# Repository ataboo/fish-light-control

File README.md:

# Fish Light Control

ESP32 controlling the brightness of addressable LEDS depending on the time of day.  Intended as lighting for a fish tank.

## Hardware

- ESP32 dev kit
- WS2812B light strip
- SN74HCT04N HEX inverter

SN74HCT04N shifts the signal level from 3.3v to 5v by inverting twice.

## Install

Setup typical ESP-IDF environment (tested on IDF 4.2).  Menu options for `ESP-Fish-Light`.  Setup SSID/PW for time synchronizations. Set sunrise/set start/end in format `hhmm`.  Set timezone according to POSIX rules.  Set color of full brightness.

## Behaviour

Device will sleep until the start of sunrise or sunset, then wake every minute to update the color during the transitions.  WIFI will be activated on first start as time establishment is required, then after light update if 24 hours has passed since the last update.

Blue lights mean initial loading/time sync.  Red lights mean failed initial load.

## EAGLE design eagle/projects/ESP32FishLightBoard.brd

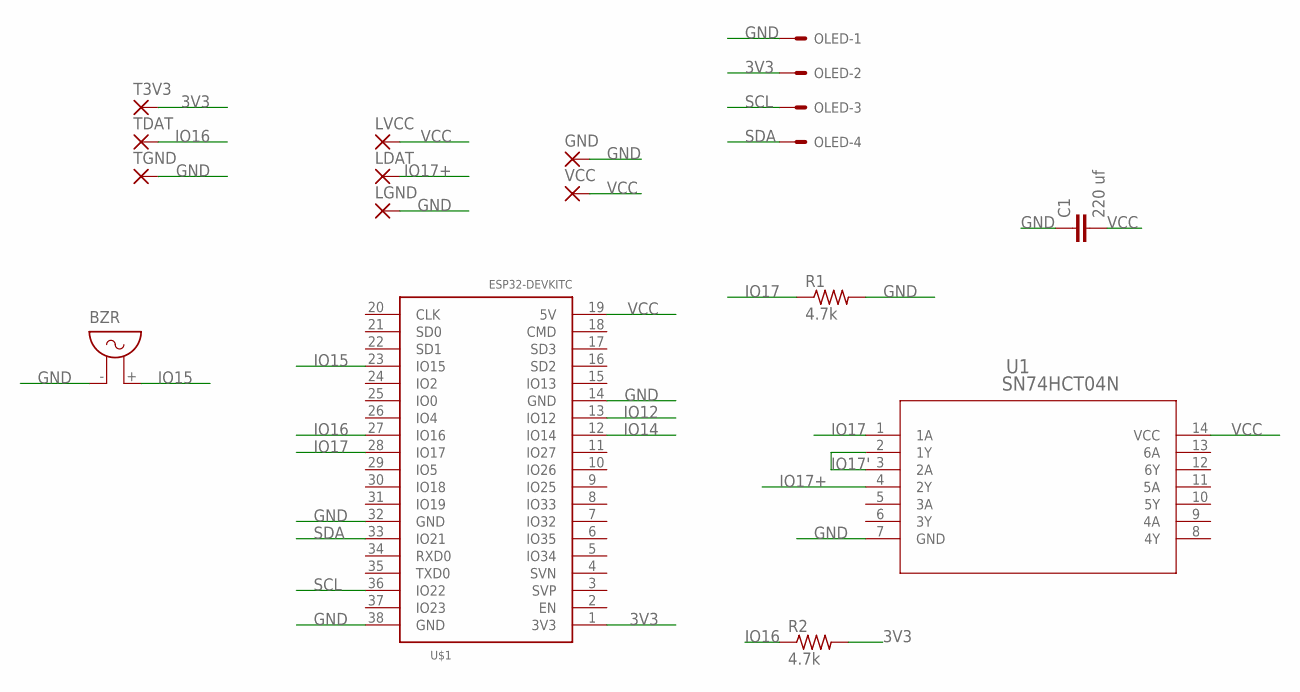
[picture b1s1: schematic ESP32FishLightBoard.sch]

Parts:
BZR: F/QMX
C1: 220 uf; C2.5-3
GND: WIREPAD2,54/1,0; 2,54/1,0
LDAT: WIREPAD2,54/1,0; 2,54/1,0
LGND: WIREPAD2,54/1,0; 2,54/1,0
LVCC: WIREPAD2,54/1,0; 2,54/1,0
OLED: 22-27-2041-04; 6410-04
R1, R2: 4.7k; 0805-THM
T3V3: WIREPAD2,54/1,0; 2,54/1,0
TDAT: WIREPAD2,54/1,0; 2,54/1,0
TGND: WIREPAD2,54/1,0; 2,54/1,0
U1: SN74HCT04N; N14
U$1: ESP32DEVKITC-LIGHT; ESP32-DEVKITC-LIGHT
VCC: WIREPAD2,54/1,0; 2,54/1,0

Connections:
3V3: OLED.2, R2.2, T3V3.1, U$1.1 (3V3)
GND: BZR.- (1), C1.1, GND.1, LGND.1, OLED.1, R1.2, TGND.1, U1.7 (GND), U$1.14 (GND), U$1.32 (GND), U$1.38 (GND)
IO12: U$1.13 (IO12)
IO14: U$1.12 (IO14)
IO15: BZR.+ (2), U$1.23 (IO15)
IO16: R2.1, TDAT.1, U$1.27 (IO16)
IO17: R1.1, U1.1 (1A), U$1.28 (IO17)
IO17': U1.2 (1Y), U1.3 (2A)
IO17+: LDAT.1, U1.4 (2Y)
SCL: OLED.3, U$1.36 (IO22)
SDA: OLED.4, U$1.33 (IO21)
VCC: C1.2, LVCC.1, U1.14 (VCC), U$1.19 (5V), VCC.1

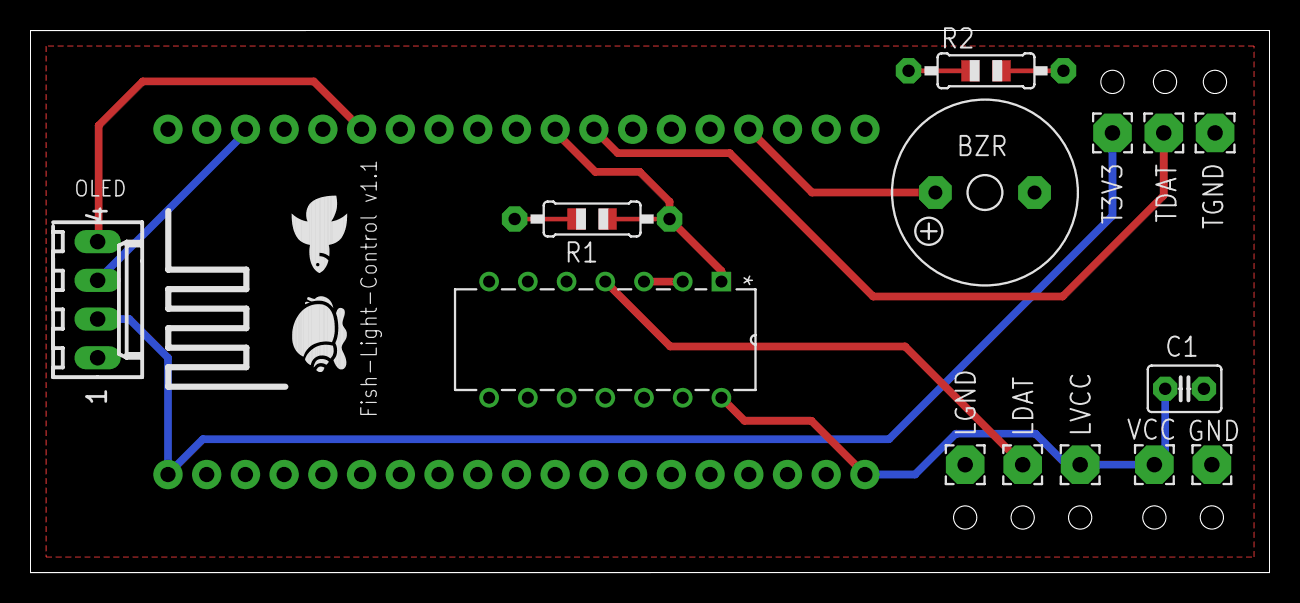
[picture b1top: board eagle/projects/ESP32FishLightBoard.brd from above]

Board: 2 copper layers, 81.3 x 35.6 mm, 15 parts (0 on the bottom side), 10 nets.

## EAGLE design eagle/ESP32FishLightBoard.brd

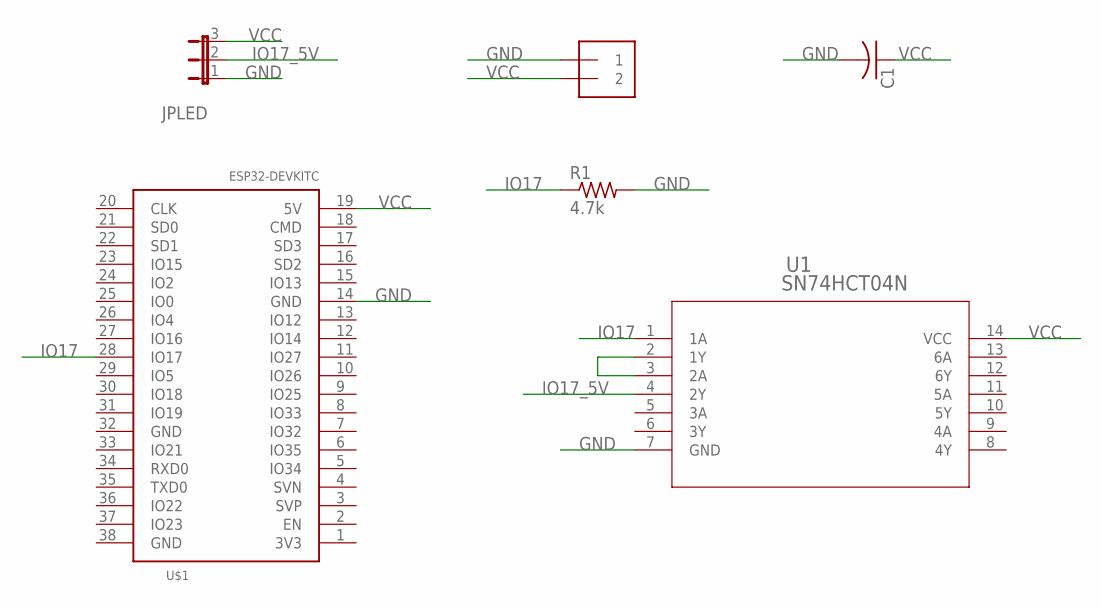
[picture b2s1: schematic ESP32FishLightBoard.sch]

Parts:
C1: C-US025-040X050; C025-040X050
J1: 1X2-3.5MM
JPLED: JP2E; JP2
R1: 4.7k; 0805-THM
U1: SN74HCT04N; N14
U$1: ESP32DEVKITC; ESP32-DEVKITC

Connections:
GND: C1.2, J1.1, JPLED.1, R1.2, U1.7 (GND), U$1.14 (GND)
IO17: R1.1, U1.1 (1A), U$1.28 (IO17)
IO17_5V: JPLED.2, U1.4 (2Y)
unnamed: U1.2 (1Y), U1.3 (2A)
VCC: C1.1, J1.2, JPLED.3, U1.14 (VCC), U$1.19 (5V)

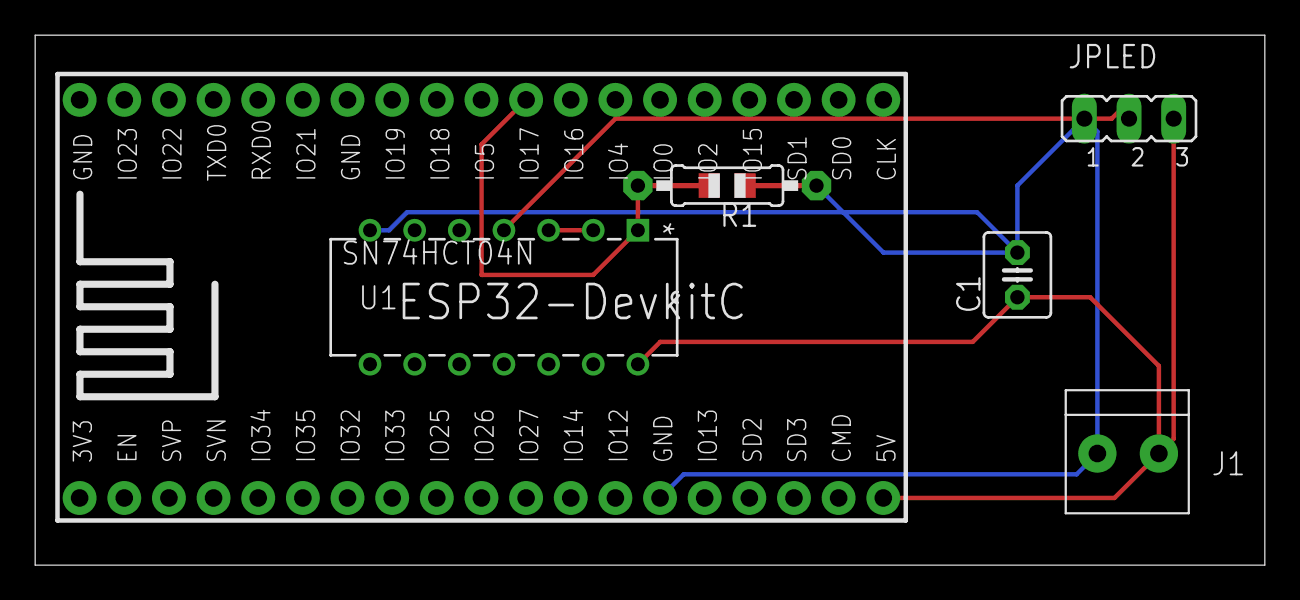
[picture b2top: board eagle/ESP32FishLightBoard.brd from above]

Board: 2 copper layers, 70.0 x 30.1 mm, 6 parts (0 on the bottom side), 5 nets.

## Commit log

2021-02-21 Added fetching time
2021-02-22 added ws2812, working on resetting wifi
2021-02-23 fixed wifi restart, refactored to scheduler
2021-02-23 added readme
2021-02-25 adjusted light color, removed debugging
2021-02-25 added pull-down resistor to board
2021-03-14 updated eagle board
2021-03-23 stopped diffing color change
2021-04-21 updated to v1.1 PCB
2021-04-22 Added esp-ssd-1306 as submodule
2021-04-24 adding display control layr
2021-04-25 adding display control
2021-04-25 working on display control
2021-04-29 added temp sensor reading
2021-05-07 Adding eagle for v1.1 board
2021-05-08 adding buzzer, more display things
2021-05-12 added buzzer music translation
